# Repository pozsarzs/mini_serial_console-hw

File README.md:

**Mini serial console with 20x4 LCD, six buttons and three different ports**  
Copyright (C) 2022 Pozsár Zsolt <pozsarzs@gmail.com>  
Homepage: <http://www.pozsarzs.hu>  
GitHub: <https://github.com/pozsarzs/mini_serial_console-hw>

**Documentation**

- version:             1.0
- language:            en
- licence:             CC-BY-NC-4.0

**Hardware**

 - version:            v220726

**Content of CAD folders**

cad_files/Fritzing:      wiring of the breadboards  
cad_files/KiCAD:         schematic and PCB drawings, Gerber files  
cad_files/LibreCAD:      drawing of the polycarbonate cover

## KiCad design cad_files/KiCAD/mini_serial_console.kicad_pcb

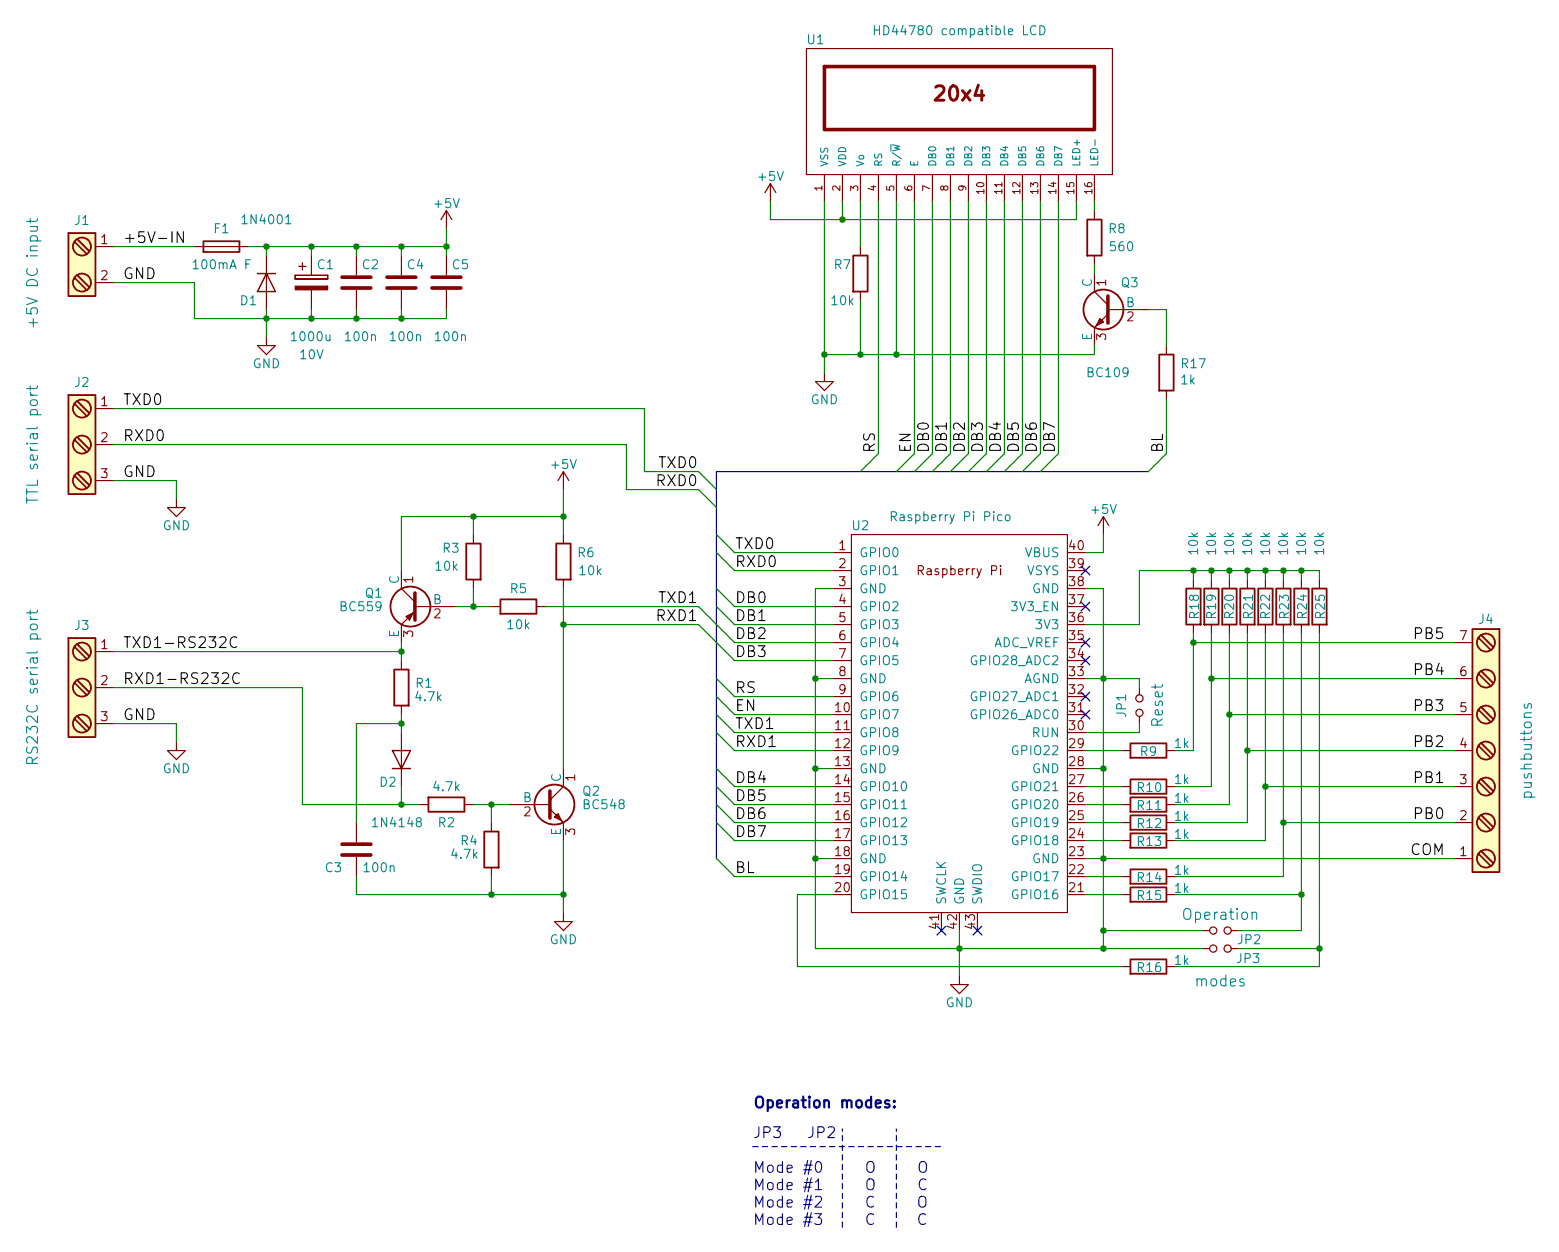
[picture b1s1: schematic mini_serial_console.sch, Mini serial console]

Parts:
C1: 1000u; CP_Radial_D10.0mm_P5.00mm; Voltage 10V
C2, C3, C4, C5: 100n; C_Disc_D5.0mm_W2.5mm_P5.00mm
D1: 1N4001; D_DO-41_SOD81_P10.16mm_Horizontal
D2: 1N4148; D_DO-41_SOD81_P7.62mm_Horizontal
F1: 100mA F; Fuseholder5x20_simple_metal
J1: Screw_Terminal_1x02; bornier2
J2, J3: Screw_Terminal_1x03; bornier3
J4: Screw_Terminal_1x07; bornier7
JP1, JP2, JP3: Jumper_NO_Small; Socket_Strip_Straight_1x02
Q1: BC559; TO-92_Inline_Narrow_Oval
Q2: BC548; TO-92_Inline_Narrow_Oval
Q3: BC109; TO-18-3
R1, R2, R4: 4.7k; R_Axial_DIN0309_L9.0mm_D3.2mm_P5.08mm_Vertical
R3, R5, R6, R7, R18, R19, R20, R21, R22, R23, R24, R25: 10k; R_Axial_DIN0309_L9.0mm_D3.2mm_P5.08mm_Vertical
R8: 560; R_Axial_DIN0309_L9.0mm_D3.2mm_P5.08mm_Vertical
R9, R10, R11, R12, R13, R14, R15, R16, R17: 1k; R_Axial_DIN0309_L9.0mm_D3.2mm_P5.08mm_Vertical
U1: HD44780 compatible LCD; Socket_Strip_Straight_1x16
U2: Raspberry Pi Pico; RPi_Pico_SMD_TH

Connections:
+5V: C1.1, C2.1, C4.1, C5.1, D1.1 (K), F1.1, Q1.1 (C), R3.1, R6.1, U1.2 (VDD), U1.15 (LED+), U2.40 (VBUS)
/+5V-IN: F1.2, J1.1
/BL: R17.2, U2.19 (GPIO14)
/DB0: U1.7 (DB0), U2.4 (GPIO2)
/DB1: U1.8 (DB1), U2.5 (GPIO3)
/DB2: U1.9 (DB2), U2.6 (GPIO4)
/DB3: U1.10 (DB3), U2.7 (GPIO5)
/DB4: U1.11 (DB4), U2.14 (GPIO10)
/DB5: U1.12 (DB5), U2.15 (GPIO11)
/DB6: U1.13 (DB6), U2.16 (GPIO12)
/DB7: U1.14 (DB7), U2.17 (GPIO13)
/EN: U1.6 (E), U2.10 (GPIO7)
/PB0: J4.2, R14.1, R23.2
/PB1: J4.3, R13.1, R22.2
/PB2: J4.4, R12.1, R21.2
/PB3: J4.5, R11.1, R20.2
/PB4: J4.6, R10.1, R19.2
/PB5: J4.7, R9.1, R18.2
/RS: U1.4 (RS), U2.9 (GPIO6)
/RXD0: J2.2, U2.2 (GPIO1)
/RXD1: Q2.1 (C), R6.2, U2.12 (GPIO9)
/RXD1-RS232C: D2.1 (K), J3.2, R2.2
/TXD0: J2.1, U2.1 (GPIO0)
/TXD1: R5.1, U2.11 (GPIO8)
/TXD1-RS232C: J3.1, Q1.3 (E), R1.1
GND: C1.2, C2.2, C3.2, C4.2, C5.2, D1.2 (A), J1.2, J2.3, J3.3, J4.1, JP1.1, JP2.1, JP3.1, Q2.3 (E), Q3.3 (E), R4.2, R7.2, U1.1 (VSS), U1.5 (R/~W), U2.3 (GND), U2.8 (GND), U2.13 (GND), U2.18 (GND), U2.23 (GND), U2.28 (GND), U2.33 (AGND), U2.38 (GND), U2.42 (GND)
unnamed: C3.1, D2.2 (A), R1.2
unnamed: JP1.2, U2.30 (RUN)
unnamed: JP2.2, R15.1, R24.2
unnamed: JP3.2, R16.1, R25.2
unnamed: Q1.2 (B), R3.2, R5.2
unnamed: Q2.2 (B), R2.1, R4.1
unnamed: Q3.1 (C), R8.2
unnamed: Q3.2 (B), R17.1
unnamed: R7.1, U1.3 (Vo)
unnamed: R8.1, U1.16 (LED-)
unnamed: R9.2, U2.29 (GPIO22)
unnamed: R10.2, U2.27 (GPIO21)
unnamed: R11.2, U2.26 (GPIO20)
unnamed: R12.2, U2.25 (GPIO19)
unnamed: R13.2, U2.24 (GPIO18)
unnamed: R14.2, U2.22 (GPIO17)
unnamed: R15.2, U2.21 (GPIO16)
unnamed: R16.2, U2.20 (GPIO15)
unnamed: R18.1, R19.1, R20.1, R21.1, R22.1, R23.1, R24.1, R25.1, U2.36 (3V3)

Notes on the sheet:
JP3 JP2 Mode #0 O O Mode #1 O C Mode #2 C O Mode #3 C C
Operation modes:

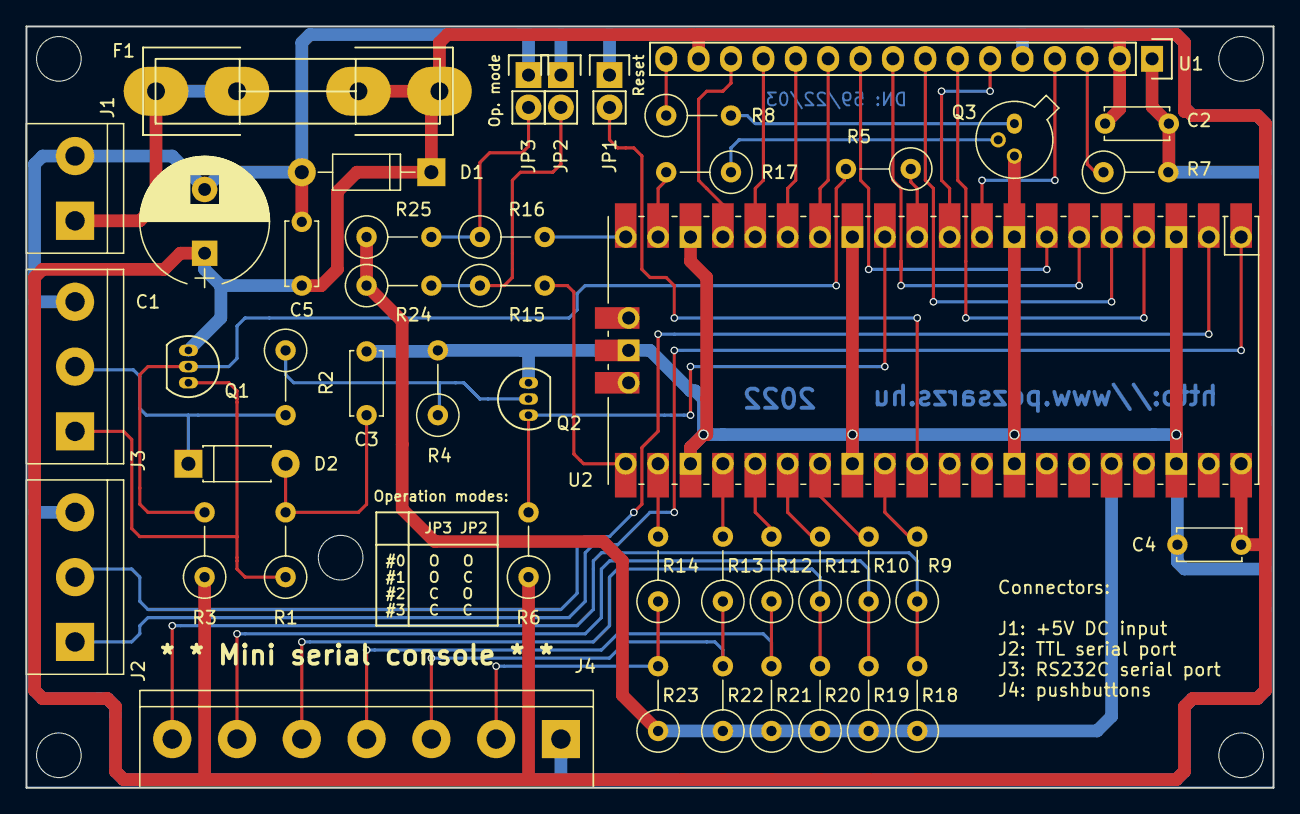
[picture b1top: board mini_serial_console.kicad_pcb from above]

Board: 2 copper layers, 97.8 x 59.7 mm, 50 parts (0 on the bottom side), 45 nets.

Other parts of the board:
MH1, MH2, MH3, MH4, MH5: MountingHole_3.5mm

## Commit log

2022-07-27 220727
2022-07-30 220730
2022-09-29 220929
2022-09-30 220930
2022-10-01 221001
2022-10-09 221009
2022-10-17 2210117
2022-10-18 221018
2022-10-20 221020
2022-11-15 221115
2022-11-21 221121
2022-11-24 221124
2022-11-30 221130
2022-12-01 221201
